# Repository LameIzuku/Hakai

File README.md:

# Hakai

Hardware, firmware-adjacent tooling and web assets for the Hakai mouse.

## Repository layout

```
hardware/            KiCad projects, one folder per design revision
  rev2/                Jul 2026  - hakai_mouse_rev2
  v5/                  Jul 2026  - hakai_mouse_v5
  final/               Jul 2026  - hakai_mouse_final
  v6/                  Jul 2026  - hakai_mouse_v6
  v6-final-v2/         Aug 2026  - hakai_mouse_v6   <-- CURRENT / authoritative
site/                Product site (static HTML + assets)
docs/                Design notes and schematic write-ups
tools/               Helper scripts (Blender MCP addon, etc.)
archive/             Local-only zip snapshots (not tracked - see .gitignore)
```

Revision order is chronological by board file date. **`hardware/v6-final-v2/` is
the authoritative design**; the other folders are kept for history and should not
be fabricated from.

## Current board: `hardware/v6-final-v2`

| | |
|---|---|
| Board            | 70.10 x 110.10 mm, 2 layer, 0.8 mm |
| Copper           | 1 oz (35 um) both outer layers |
| Min track / clearance | 0.10 mm / 0.072 mm (QFN courtyards only; 0.20 mm elsewhere) |
| Min drill        | 0.20 mm |
| Mounting holes   | 3x NPTH 3.2 mm at (114,72), (155,130), (160,74) |

### Assembly note - MH3

MH3 is the NPTH 3.2 mm hole at **(155.000, 130.000)**. The ground pour is held
back 1.40 mm from the hole edge by a dedicated keepout. **Fit a nylon or other
insulating washer / standoff at MH3** - do not use a bare metal washer.

### Fabrication status: READY

The saved zone fill is current. Verified with KiCad 10.0.5:

- DRC **without** `--refill-zones` (i.e. against the *stored* fill that gerber
  export actually plots): **0 violations, 0 unconnected**
- Ground pour clearance to the MH3 hole edge: **1.3964 mm (F.Cu) / 1.3974 mm
  (B.Cu)**, measured in the exported gerber
- Mounting-hole drill: 3x NPTH 3.2 mm, MH3 at `X155.0 Y-130.0`

Ready-to-send package: **`gerbers/fab_ready/`** - 9 gerbers, merged Excellon
drill (PTH + NPTH, MixedPlating), `.gbrjob`, and `FAB_NOTES.txt`.

> **Always re-fill zones before exporting gerbers.** Gerber export plots the
> *saved* fill, not a live one. If you edit routing, run `Edit > Fill All Zones`
> (B), confirm DRC is 0/0 with "Refill all zones" *unchecked*, then save and
> re-export. An earlier revision of this board shipped a stale fill in which the
> GND pour overlapped SWDIO and VBAT_SENSE at 0.0000 mm clearance.

### Known deviation - VBAT_SENSE under the RF feed

`VBAT_SENSE` on B.Cu crosses beneath `RF_FEED` on F.Cu, with the nearest plane
cut **~1.79 mm from the antenna feed pad ANT1.1** at (138.000, 140.000).
Crossing counts are unchanged from the pre-reroute baseline (2x RF_FEED, 2x ANT,
1x RF1, all broadside through the 0.8 mm dielectric), but the baseline's closest
cut was 8.83 mm out. Accepted for prototype. If return loss disappoints, look
here before touching the match component values.

## Excluded from version control

| Excluded | Size | Why |
|---|---|---|
| `archive/*.zip` | 163 MB + 64 MB | Self-archives of this tree; the 163 MB file exceeds GitHub's 100 MB hard limit |
| `**/tools/fr/*.jar` | 58 MB each | Freerouting - download from [freerouting/freerouting](https://github.com/freerouting/freerouting/releases) |
| `.history/` | - | VS Code Local History; contains nested git repos |
| `*.kicad_prl` | - | Per-user KiCad local settings |

`.gitattributes` sets `* -text` so git never rewrites line endings. Gerber and
drill files are checksum-verified; EOL conversion would silently corrupt them.

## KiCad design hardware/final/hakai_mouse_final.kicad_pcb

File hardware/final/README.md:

# HAKAI Wireless Gaming Mouse — FINAL Release Package (v5.3)

> **v5.3 — sensor/switch mechanicals brought to datasheet-exact, ADC margin doubled:**
> 1. **PAW3311 board features now EXACT per PixArt Table 9 (L0AJ-LSG1 column):** the aperture
>    cutout grows to its true size (x −7.86…+1.64 with the optical-axis notch out to −9.56,
>    y 1.38…11.23, corners R0.40 max — the v5.2 rect was undersized and the lens tower would
>    not have fit); the LED cutout is the real **R0.90 × 2.00 stadium** (was a R0.65 placeholder);
>    the **2× lens guide-post holes** (2.0 × 1.6, R0.40, x 4.58…6.58) are added — the L0AJ lens
>    self-aligns through these and can be heat-staked (PixArt assembly note 8); sensor pin holes
>    are Ø0.80 per the drawing. **D2 now uses a custom footprint** whose pads sit at the Table 9
>    "LED Soldering Pad" positions, 0.12 mm clear of the stadium (a generic 1206 would violate
>    copper-to-edge). C26/C27/R23 moved slightly to clear the new cutouts. **Verify D2's pads
>    against the final PixArt-recommended IR-LED P/N before fab.**
> 2. **Kailh boss-hole question CLOSED — no holes needed:** official Omron D2F + D2FC datasheets
>    and the Kailh GM 8.0 drawing all show a **flat switch bottom**; the "two holes" in those
>    drawings are side-face chassis-pin features 1.5 mm above the PCB. Omron's PCB pattern is
>    3× Ø1.2 terminal holes at 5.08 pitch — the footprint now matches it exactly, and its
>    silk/courtyard is fixed to the true centered 12.8 × 5.8 body (plunger marked on F.Fab).
> 3. **R25 = 47 k (was 100 k):** Q1's worst-case off-state leakage (5 µA) × 47 k = 0.24 V,
>    comfortably under Q3's 0.5 V minimum gate threshold — the paper margin that was zero at
>    100 k is now 2×. Sampling current rises to ~103 µA, still only while P0.03 is high.
> 4. **Placement + silkscreen corrections from the adversarial re-review of this revision:**
>    TP1–TP6 raised to y = 43.5 (SW2's corrected courtyard overlapped the old row and the
>    switch body would have blocked probing); SW4 moved to x = 107.2 (its true-size body
>    overhung the x = 104 board edge); R22/C35/R23 relocated to the open band below the
>    sensor (y = 115.5), fully vacating the PixArt clear zone so only U5 features + the IR
>    LED live inside the lens region; Kailh plunger marker set to x = −1.95 per the verified
>    drawings. **Silkscreen cleaned up:** custom-footprint reference designators repositioned
>    off their own pads/cutouts, the U5 body outline redrawn so it no longer crosses the
>    aperture/notch/stadium cutouts, D2 and the M3-hole refs moved to F.Fab (they sit under
>    the lens / are board-only). DRC silk warnings dropped from 38 → **4** (all harmless
>    refdes-text overlaps in the two densest corners; 0 error-severity violations besides the
>    intentional unrouted ratsnest).

> **v5.2:** C36 (10 µF) added at the BQ24074 BAT pins (Table 7-1 mandatory bypass);
> battery-sense divider re-topologized to **high-side gating** (Q3 AO3401A + R25, Q1 drives the
> gate) so AIN0 can never float above VDD and standby drain is truly zero. New nets `VBAT_SW`,
> `VBAT_SW_G`. **v5.1:** middle click = 5th Kailh GM 8.0 (SW5).

nRF52833 (integrated 2.4 GHz radio) · PixArt PAW3311DB (datasheet-verified wiring **and**
mechanicals) · 5× Kailh GM 8.0 · **split scroll wheel** (EC1 encoder + SW5 Kailh) · BQ24074
charger · **single 1.9 V system rail** · shaped mouse-plate PCB with open wheel bay.

## Contents

| File | What |
|---|---|
| `hakai_mouse_final.kicad_pro` | **Open this** in KiCad 8/9/10 |
| `hakai_mouse_final.kicad_sch` | Schematic, Rev 5.3. ERC = 0 |
| `hakai_mouse_final.kicad_pcb` | Shaped board: all footprints placed + full net assignment. **UNROUTED** |
| `hakai_mouse_final_schematic.pdf` | Plotted schematic for review |
| `board_top_render.png` | 3D top view of the board |
| `BOM_hakai_mouse_final.csv` | Grouped bill of materials (kicad-cli export) |
| `Cost_Estimate_hakai_mouse_final.csv` | Per-part cost estimates + totals (≈$18.39 parts / ≈$24.89 w/ battery) |
| `DATASHEET_hakai_mouse_final.pdf` | Product-level engineering datasheet (HAKAI M1) |
| `footprints.pretty/` + `fp-lib-table` | Custom footprints: PAW3311 iDIP-8 (full Table 9 features), IR-LED pads, Kailh GM8/D2F (verified pattern), 11 mm encoder |
| `datasheets/PAW3311DB-T2MU_v1.0.pdf` | PixArt datasheet — source of all sensor wiring + Table 9 mechanicals |
| `verification/` | ERC report, DRC report, netlist cross-check, pad-by-pad electrical audit |
| `tools/` | Python generators + checkers that build this project (run with KiCad's bundled python) |
| `build/` | Intermediate netlist (`net.net`) used by the board generator and checkers |

## v5 design highlights

- **Split scroll wheel (type B, like commercial mice):** EC1 = 11 mm rotation-only encoder on the
  **left wheel-bay wall** (D-socket accepts the wheel axle, shaft points into the bay);
  SW5 = **Kailh GM 8.0** on the **right wall** — the wheel cradle presses it for middle click,
  giving M3 the same tactility as the main buttons.
  Nets/pins: `ENC_A`→P0.08, `ENC_B`→P0.11 (nRF QDEC-compatible), `ENC_SW`→P0.12, all with 10 k pull-ups.
  Wheel/axle/cradle are shell parts, not PCB items.
- **Single 1.9 V rail** (XC6219B192MR): PAW3311 VDD abs max is 2.1 V — 3.3 V anywhere on the sensor
  is fatal; the nRF52833 runs 1.7–3.6 V so MCU + sensor share the rail, no level shifting.
  Status LED runs from VSYS via Q2 (AO3400A); SWD debug is 1.9 V logic (set probe VTref).
- **Sensor verified against the real datasheet** (v1.0, 1A009EN) — electrically *and*
  mechanically: 3-wire SDIO with the MISO-direct / MOSI-via-3.3 k bridge (R23; 1 k @ 4 MHz,
  240 Ω @ 8 MHz), VDDREG bypass-only (4.7 µF/10 V + 100 nF), MOTION push-pull, LED chain
  1V9 → 18 Ω 1% → IR LED → pin 1 (24 mA); board features exact per Table 9 (aperture + notch,
  LED stadium, guide-post holes, Ø0.80 pin holes, 0.8 mm PCB).
- **Board**: 70 × 110 mm envelope, 0.8 mm thick (sensor lens stack requires it), 2-layer.
  Open U wheel bay 24 × 38 mm between switch ears; chamfered corners; narrowed tail with
  **USB-C charge port at the tail edge**; sensor aperture/LED/guide-post cutouts inside the U5
  footprint (optical center at 135, 106); TI SWRA117D PCB antenna in a copper-free tail zone;
  3× M3 mounting holes; GND pour both layers.
- **nRF52833 support circuitry verified** against Nordic PS v1.7 + PCA10100 DK files:
  DEC3 = 100 pF (not 100 nF), DEC4+DEC6 tied (1 µF + 47 nF), DC/DC 10 µH + 15 nH,
  RF match 1.0 pF / 4.7 nH / 1.2 pF / 2.2 nH + antenna-dependent tune cap (DNP).
  BQ24074: ILIM mode 497 mA input / 445 mA charge, TS 10 k fixed, TMR/ITERM float,
  BAT bypassed by C36 10 µF at pins 2/3 (v5.2).

## Verification shipped in `verification/`

- `ERC_report.rpt` — 0 violations
- `netlist_crosscheck.txt` — 45 signal nets + 6 rails exact-match against the design intent
- `pad_audit.txt` — **every PCB pad's net compared to the schematic netlist: 0 mismatches**
  (die pad / USB shield / crystal shell / antenna stub / encoder brackets are the verified,
  whitelisted board-side extras)
- `DRC_report.rpt` — 0 error-severity violations besides the intentional unrouted ratsnest
  (KiCad rates each of the 143 missing connections as an error; the only other entries are
  4 silk-cosmetic warnings — refdes-text overlaps in the two densest corners, no electrical,
  clearance, or solder-mask impact)
- Geometric containment: every pad verified inside the shaped outline

## Before fab (the honest list)

1. **Route it** — the board is placed + netted, deliberately unrouted. RF path (nRF ANT →
   1.0 pF/4.7 nH/1.2 pF/2.2 nH → antenna): copy Nordic PCA10100 trace/ground geometry verbatim,
   50 Ω, stitch vias, then VNA-tune C24.
2. **EC1 vendor check** — pin/bracket spacing is a generic 11 mm pattern; verify against the exact
   TTC / F-switch drawing you buy.
3. **SW5 actuation** — shell cradle press travel must match the Kailh's plunger height/force
   (plunger end faces the bay); a GM 4.0 swap is drop-in if M3 ends up too easy to trigger.
4. **IR LED P/N** — D2's pads follow PixArt Table 9; confirm them against the reflow pad
   recommendation of the actual emitter you buy (PixArt names the P/N for the L0AJ-LSG1 set).
5. **Battery polarity** — JST PH has no standard; this design says pin 1 = BAT+. Verify the pigtail
   with a DMM. Use a protected cell.

*(Closed in v5.3: the old "enlarge LED cutout" item — now datasheet-exact — and the old "add
Kailh boss holes" item — investigated against official Omron/Kailh drawings; the switches have
flat bottoms and no boss holes exist to add.)*

## Firmware bring-up notes

- SPI mode 3, start ≤2 MHz (matches R23 = 3.3 k). Wake-from-shutdown needs RESET + 50 ms (tMOT-RST).
- Scroll decoding: nRF52833 **QDEC** peripheral on P0.08/P0.11; LED pin on P0.13 gates Q2 from VSYS.
- nRESET = P0.18 via UICR PSELRESET; DC/DC REG1 enabled (L fitted). Battery ADC: AIN0; drive
  P0.03 **high** to sample (Q1 pulls Q3's gate low → P-FET connects VBAT to the divider; adds
  ~103 µA through R25 + divider only while sampling). P0.03 low/high-Z = divider fully dead,
  AIN0 held at GND by R9 — true zero standby drain.

## Regenerating (reproducible build)

`tools/` contains the deterministic generators: `gen_kicad.py` (schematic), `pcb_gen.py` (board),
plus the checkers (`check_netlist.py`, `pcb_check.py`, `verify_pkg.py`, `drc_summary.py`). All
paths are **package-relative** as of v5.2 — no editing needed. Run with KiCad's bundled Python
(`C:\Program Files\KiCad\10.0\bin\python.exe`):

```
python tools/gen_kicad.py                                # rebuild schematic
kicad-cli sch export netlist --output build/net.net hakai_mouse_final.kicad_sch
python tools/pcb_gen.py                                  # rebuild board (reads build/net.net)
python tools/fill_zones.py                               # refill GND pours
python tools/check_netlist.py                            # netlist vs design intent
python tools/pcb_check.py                                # pad-by-pad PCB vs netlist audit
python tools/verify_pkg.py                               # containment/BOM/cost/inventory
```

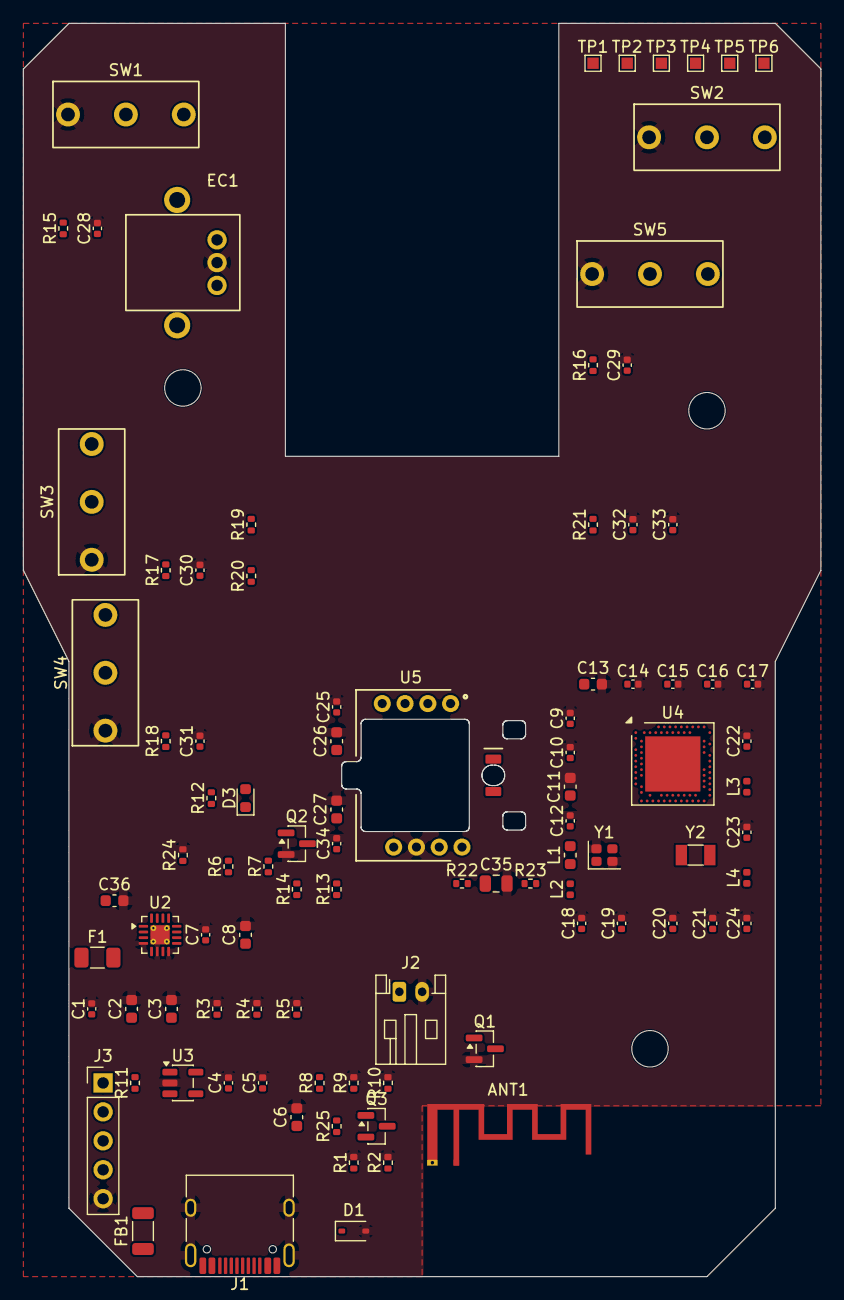
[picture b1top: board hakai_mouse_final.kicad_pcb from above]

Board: 2 copper layers, 70.0 x 110.0 mm, 98 parts (0 on the bottom side), 51 nets, no tracks yet.

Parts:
ANT1: PCB IFA 2.4GHz; Texas_SWRA117D_2.4GHz_Right
C1, C4, C5, C14: 1uF; C_0402_1005Metric
C2, C3, C6, C8, C26, C36: 10uF; C_0603_1608Metric
C7, C9, C15, C16, C17, C25, C34: 100nF; C_0402_1005Metric
C10: 100pF NP0; C_0402_1005Metric
C11: 1uF; C_0603_1608Metric
C12: 47nF; C_0402_1005Metric
C13: 4.7uF; C_0603_1608Metric
C18, C19, C20, C21: 12pF NP0; C_0402_1005Metric
C22: 1.0pF NP0; C_0402_1005Metric
C23: 1.2pF NP0; C_0402_1005Metric
C24: 1.2pF (DNP); C_0402_1005Metric
C27: 4.7uF/10V; C_0603_1608Metric
C28, C29, C30, C31: 100nF (DNP); C_0402_1005Metric
C32, C33: 10nF; C_0402_1005Metric
C35: 33uF; C_0805_2012Metric
D1: PESD5V0S1BA; D_SOD-323
D2: IR LED (SMT / L0AJ-LSG1 set); IRLED_L0AJ_3311
D3: BLUE; LED_0603_1608Metric
EC1: 11mm encoder; ENC_Mouse_11mm
F1: PTC 1A; Fuse_1206_3216Metric
FB1: 600R@100MHz; L_1206_3216Metric
J1: USB4105-GF-A; USB_C_Receptacle_HRO_TYPE-C-31-M-12
J2: JST S2B-PH-K; JST_PH_S2B-PH-K_1x02_P2.00mm_Horizontal
J3: SWD 1x05; PinHeader_1x05_P2.54mm_Vertical
L1: 10uH; L_0603_1608Metric
L2: 15nH; L_0402_1005Metric
L3: 4.7nH; L_0402_1005Metric
L4: 2.2nH; L_0402_1005Metric
MH1, MH2, MH3: M3; MountingHole_3.2mm_M3
Q1, Q2: AO3400A; SOT-23
Q3: AO3401A; SOT-23
R1, R2: 5.1k; R_0402_1005Metric
R3, R11, R13, R15, R16, R17, R18, R19, R20, R21: 10k; R_0402_1005Metric
R4: 3.24k; R_0402_1005Metric
R5: 2.0k; R_0402_1005Metric
R6, R7, R9, R10, R24: 100k; R_0402_1005Metric
R8: 200k; R_0402_1005Metric
R12: 1k; R_0402_1005Metric
R14: 10k (DNP); R_0402_1005Metric
R22: 18R 1%; R_0402_1005Metric
R23: 3.3k 1%; R_0402_1005Metric
R25: 47k; R_0402_1005Metric
SW1, SW2, SW3, SW4, SW5: Kailh GM 8.0; SW_Kailh_GM8_D2F
TP1: TP1; TestPoint_Pad_1.0x1.0mm
TP2: TP2; TestPoint_Pad_1.0x1.0mm
TP3: TP3; TestPoint_Pad_1.0x1.0mm
TP4: TP4; TestPoint_Pad_1.0x1.0mm
TP5: TP5; TestPoint_Pad_1.0x1.0mm
TP6: TP6; TestPoint_Pad_1.0x1.0mm
U2: BQ24074; VQFN-16-1EP_3x3mm_P0.5mm_EP1.68x1.68mm_ThermalVias
U3: XC6219B192MR; SOT-23-5
U4: nRF52833-QIAA (Bxx+); Nordic_AQFN-73-1EP_7x7mm_P0.5mm
U5: PAW3311DB-T2MU; PAW3311DB_iDIP8_L0AJ
Y1: 32MHz CL=8pF; Crystal_SMD_2016-4Pin_2.0x1.6mm
Y2: 32.768kHz CL=9pF; Crystal_SMD_3215-2Pin_3.2x1.5mm

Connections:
1V9: C5.1, C6.1, FB1.1, U3.5
1V9_A: C7.1, C8.1, C13.1, C14.1, C15.1, C16.1, C17.1, C25.1, C26.1, C35.1, FB1.2, J3.1, R6.1, R7.1, R11.1, R13.1, R14.1, R15.1, R16.1, R17.1, R18.1, R19.1, R20.1, R21.1, R22.1, U4.A22, U4.AD14, U4.AD23, U4.B1, U4.W1, U4.Y2, U5.3
ANT: C22.1, L3.1, U4.H23
BTN_LEFT: C28.1, R15.2, SW1.2, U4.J1
BTN_RIGHT: C29.1, R16.2, SW2.2, U4.K2
BTN_SIDE_BACK: C30.1, R17.2, SW3.2, U4.L1
BTN_SIDE_FWD: C31.1, R18.2, SW4.2, U4.M2
CC1: J1.A5, R1.1
CC2: J1.B5, R2.1
DCC: L1.1, U4.B3
DCC_L: L1.2, L2.1
DEC1: C9.1, U4.C1
DEC3: C10.1, U4.D23
DEC4_6: C11.1, C12.1, L2.2, U4.B5, U4.E24
ENC_A: C32.1, EC1.A, R19.2, U4.N1
ENC_B: C33.1, EC1.B, R20.2, U4.T2
ENC_SW: R21.2, SW5.2, U4.U1
GND: ANT1.2, C1.2, C2.2, C3.2, C4.2, C5.2, C6.2, C7.2, C8.2, C9.2, C10.2, C11.2, C12.2, C13.2, C14.2, C15.2, C16.2, C17.2, C18.2, C19.2, C20.2, C21.2, C22.2, C23.2, C24.2, C25.2, C26.2, C27.2, C28.2, C29.2, C30.2, C31.2, C32.2, C33.2, C34.2, C35.2, C36.2, D1.2, EC1.C, J1.A1, J1.A12, J1.B1, J1.B12, J1.SH, J2.2, J3.5, Q1.2, Q2.2, R1.2, R2.2, R3.2, R4.2, R5.2, R9.2, R10.2, R24.2, SW1.1, SW2.1, SW3.1, SW4.1, SW5.1, U2.4, U2.6, U2.8, U2.17, U3.2, U4.B7, U4.EP, U4.F23, U5.6, Y1.2, Y1.4
ILIM: R4.1, U2.12
ISET: R5.1, U2.16
LDO_IN: C4.1, F1.2, U3.1, U3.3
LED_A: D3.1, R12.2
LED_DRV: D2.1, R22.2
LED_K: D3.2, Q2.3
LED_STAT: Q2.1, R24.1, U4.AD8
PGOOD: R7.2, U2.7, U4.AD10
RF1: C23.1, L3.2, L4.1
RF_FEED: ANT1.1, C24.1, L4.2
SENS_LED: D2.2, U5.1
SENS_MOTION: R14.2, TP4.1, U4.A14, U5.5
SENS_NCS: R13.2, U4.AD12, U5.8
SENS_SDIO: R23.2, TP2.1, U4.AD20, U5.7
SPI_MOSI: R23.1, TP3.1, U4.AD18
SPI_SCK: TP1.1, U4.AD16, U5.4
STAT: R6.2, U2.9, U4.AC9
SWDCLK: J3.3, U4.AA24
SWDIO: J3.2, U4.AC24
TS: R3.1, U2.1
VBAT: C36.1, J2.1, Q3.2, R25.1, TP5.1, U2.2, U2.3
VBAT_EN: Q1.1, R10.1, U4.B13
VBAT_SENSE: R8.2, R9.1, U4.A12
VBAT_SW: Q3.3, R8.1
VBAT_SW_G: Q1.3, Q3.1, R25.2
VBUS: C1.1, C2.1, D1.1, J1.A4, J1.A9, J1.B4, J1.B9, U2.13
VDDREG: C27.1, C34.1, U5.2
VSYS: C3.1, F1.1, R12.1, TP6.1, U2.5, U2.10, U2.11
XC1: C18.1, U4.B24, Y1.1
XC2: C19.1, U4.A23, Y1.3
XL1: C20.1, U4.D2, Y2.1
XL2: C21.1, U4.F2, Y2.2
nRESET: J3.4, R11.2, U4.AC13

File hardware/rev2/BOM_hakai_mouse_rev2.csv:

"Refs","Value","Footprint","Qty","DNP"
"ANT1","PCB IFA 2.4GHz","RF_Antenna:Texas_SWRA117D_2.4GHz_Right","1",""
"C1,C4,C5,C14","1uF","Capacitor_SMD:C_0402_1005Metric","4",""
"C2,C3,C6,C8,C26","10uF","Capacitor_SMD:C_0603_1608Metric","5",""
"C7,C9,C15-C17,C25,C34","100nF","Capacitor_SMD:C_0402_1005Metric","7",""
"C10","100pF NP0","Capacitor_SMD:C_0402_1005Metric","1",""
"C11","1uF","Capacitor_SMD:C_0603_1608Metric","1",""
"C12","47nF","Capacitor_SMD:C_0402_1005Metric","1",""
"C13","4.7uF","Capacitor_SMD:C_0603_1608Metric","1",""
"C18-C21","12pF NP0","Capacitor_SMD:C_0402_1005Metric","4",""
"C22","1.0pF NP0","Capacitor_SMD:C_0402_1005Metric","1",""
"C23","1.2pF NP0","Capacitor_SMD:C_0402_1005Metric","1",""
"C24","1.2pF (DNP)","Capacitor_SMD:C_0402_1005Metric","1","DNP"
"C27","4.7uF/10V","Capacitor_SMD:C_0603_1608Metric","1",""
"C28-C31","100nF (DNP)","Capacitor_SMD:C_0402_1005Metric","4","DNP"
"C32,C33","10nF","Capacitor_SMD:C_0402_1005Metric","2",""
"C35","33uF","Capacitor_SMD:C_0805_2012Metric","1",""
"D1","PESD5V0S1BA","Diode_SMD:D_SOD-323","1",""
"D2","IR LED (SMT / L0AJ-LSG1 set)","LED_SMD:LED_1206_3216Metric","1",""
"D3","BLUE","LED_SMD:LED_0603_1608Metric","1",""
"EC1","11mm encoder","hakai_fp:ENC_Mouse_11mm","1",""
"F1","PTC 1A","Fuse:Fuse_1206_3216Metric","1",""
"FB1","600R@100MHz","Inductor_SMD:L_1206_3216Metric","1",""
"J1","USB4105-GF-A","Connector_USB:USB_C_Receptacle_HRO_TYPE-C-31-M-12","1",""
"J2","JST S2B-PH-K","Connector_JST:JST_PH_S2B-PH-K_1x02_P2.00mm_Horizontal","1",""
"J3","SWD 1x05","Connector_PinHeader_2.54mm:PinHeader_1x05_P2.54mm_Vertical","1",""
"L1","10uH","Inductor_SMD:L_0603_1608Metric","1",""
"L2","15nH","Inductor_SMD:L_0402_1005Metric","1",""
"L3","4.7nH","Inductor_SMD:L_0402_1005Metric","1",""
"L4","2.2nH","Inductor_SMD:L_0402_1005Metric","1",""
"Q1,Q2","AO3400A","Package_TO_SOT_SMD:SOT-23","2",""
"R1,R2","5.1k","Resistor_SMD:R_0402_1005Metric","2",""
"R3,R11,R13,R15-R21","10k","Resistor_SMD:R_0402_1005Metric","10",""
"R4","3.24k","Resistor_SMD:R_0402_1005Metric","1",""
"R5","2.0k","Resistor_SMD:R_0402_1005Metric","1",""
"R6,R7,R9,R10,R24","100k","Resistor_SMD:R_0402_1005Metric","5",""
"R8","200k","Resistor_SMD:R_0402_1005Metric","1",""
"R12","1k","Resistor_SMD:R_0402_1005Metric","1",""
"R14","10k (DNP)","Resistor_SMD:R_0402_1005Metric","1","DNP"
"R22","18R 1%","Resistor_SMD:R_0402_1005Metric","1",""
"R23","3.3k 1%","Resistor_SMD:R_0402_1005Metric","1",""
"SW1-SW4","Kailh GM 8.0","hakai_fp:SW_Kailh_GM8_D2F","4",""
"SW5","TACT_6x6","Button_Switch_THT:SW_TH_Tactile_Omron_B3F-100x","1",""
"TP1","TP1","TestPoint:TestPoint_Pad_1.0x1.0mm","1",""
"TP2","TP2","TestPoint:TestPoint_Pad_1.0x1.0mm","1",""
"TP3","TP3","TestPoint:TestPoint_Pad_1.0x1.0mm","1",""
"TP4","TP4","TestPoint:TestPoint_Pad_1.0x1.0mm","1",""
"TP5","TP5","TestPoint:TestPoint_Pad_1.0x1.0mm","1",""
"TP6","TP6","TestPoint:TestPoint_Pad_1.0x1.0mm","1",""
"U2","BQ24074","Package_DFN_QFN:VQFN-16-1EP_3x3mm_P0.5mm_EP1.68x1.68mm_ThermalVias","1",""
"U3","XC6219B192MR","Package_TO_SOT_SMD:SOT-23-5","1",""
"U4","nRF52833-QIAA (Bxx+)","Package_DFN_QFN:Nordic_AQFN-73-1EP_7x7mm_P0.5mm","1",""
"U5","PAW3311DB-T2MU","hakai_fp:PAW3311DB_iDIP8_L0AJ","1",""
"Y1","32MHz CL=8pF","Crystal:Crystal_SMD_2016-4Pin_2.0x1.6mm","1",""
"Y2","32.768kHz CL=9pF","Crystal:Crystal_SMD_3215-2Pin_3.2x1.5mm","1",""
